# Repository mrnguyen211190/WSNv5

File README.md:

# WSNv5
A small hardware of wireless sensor node

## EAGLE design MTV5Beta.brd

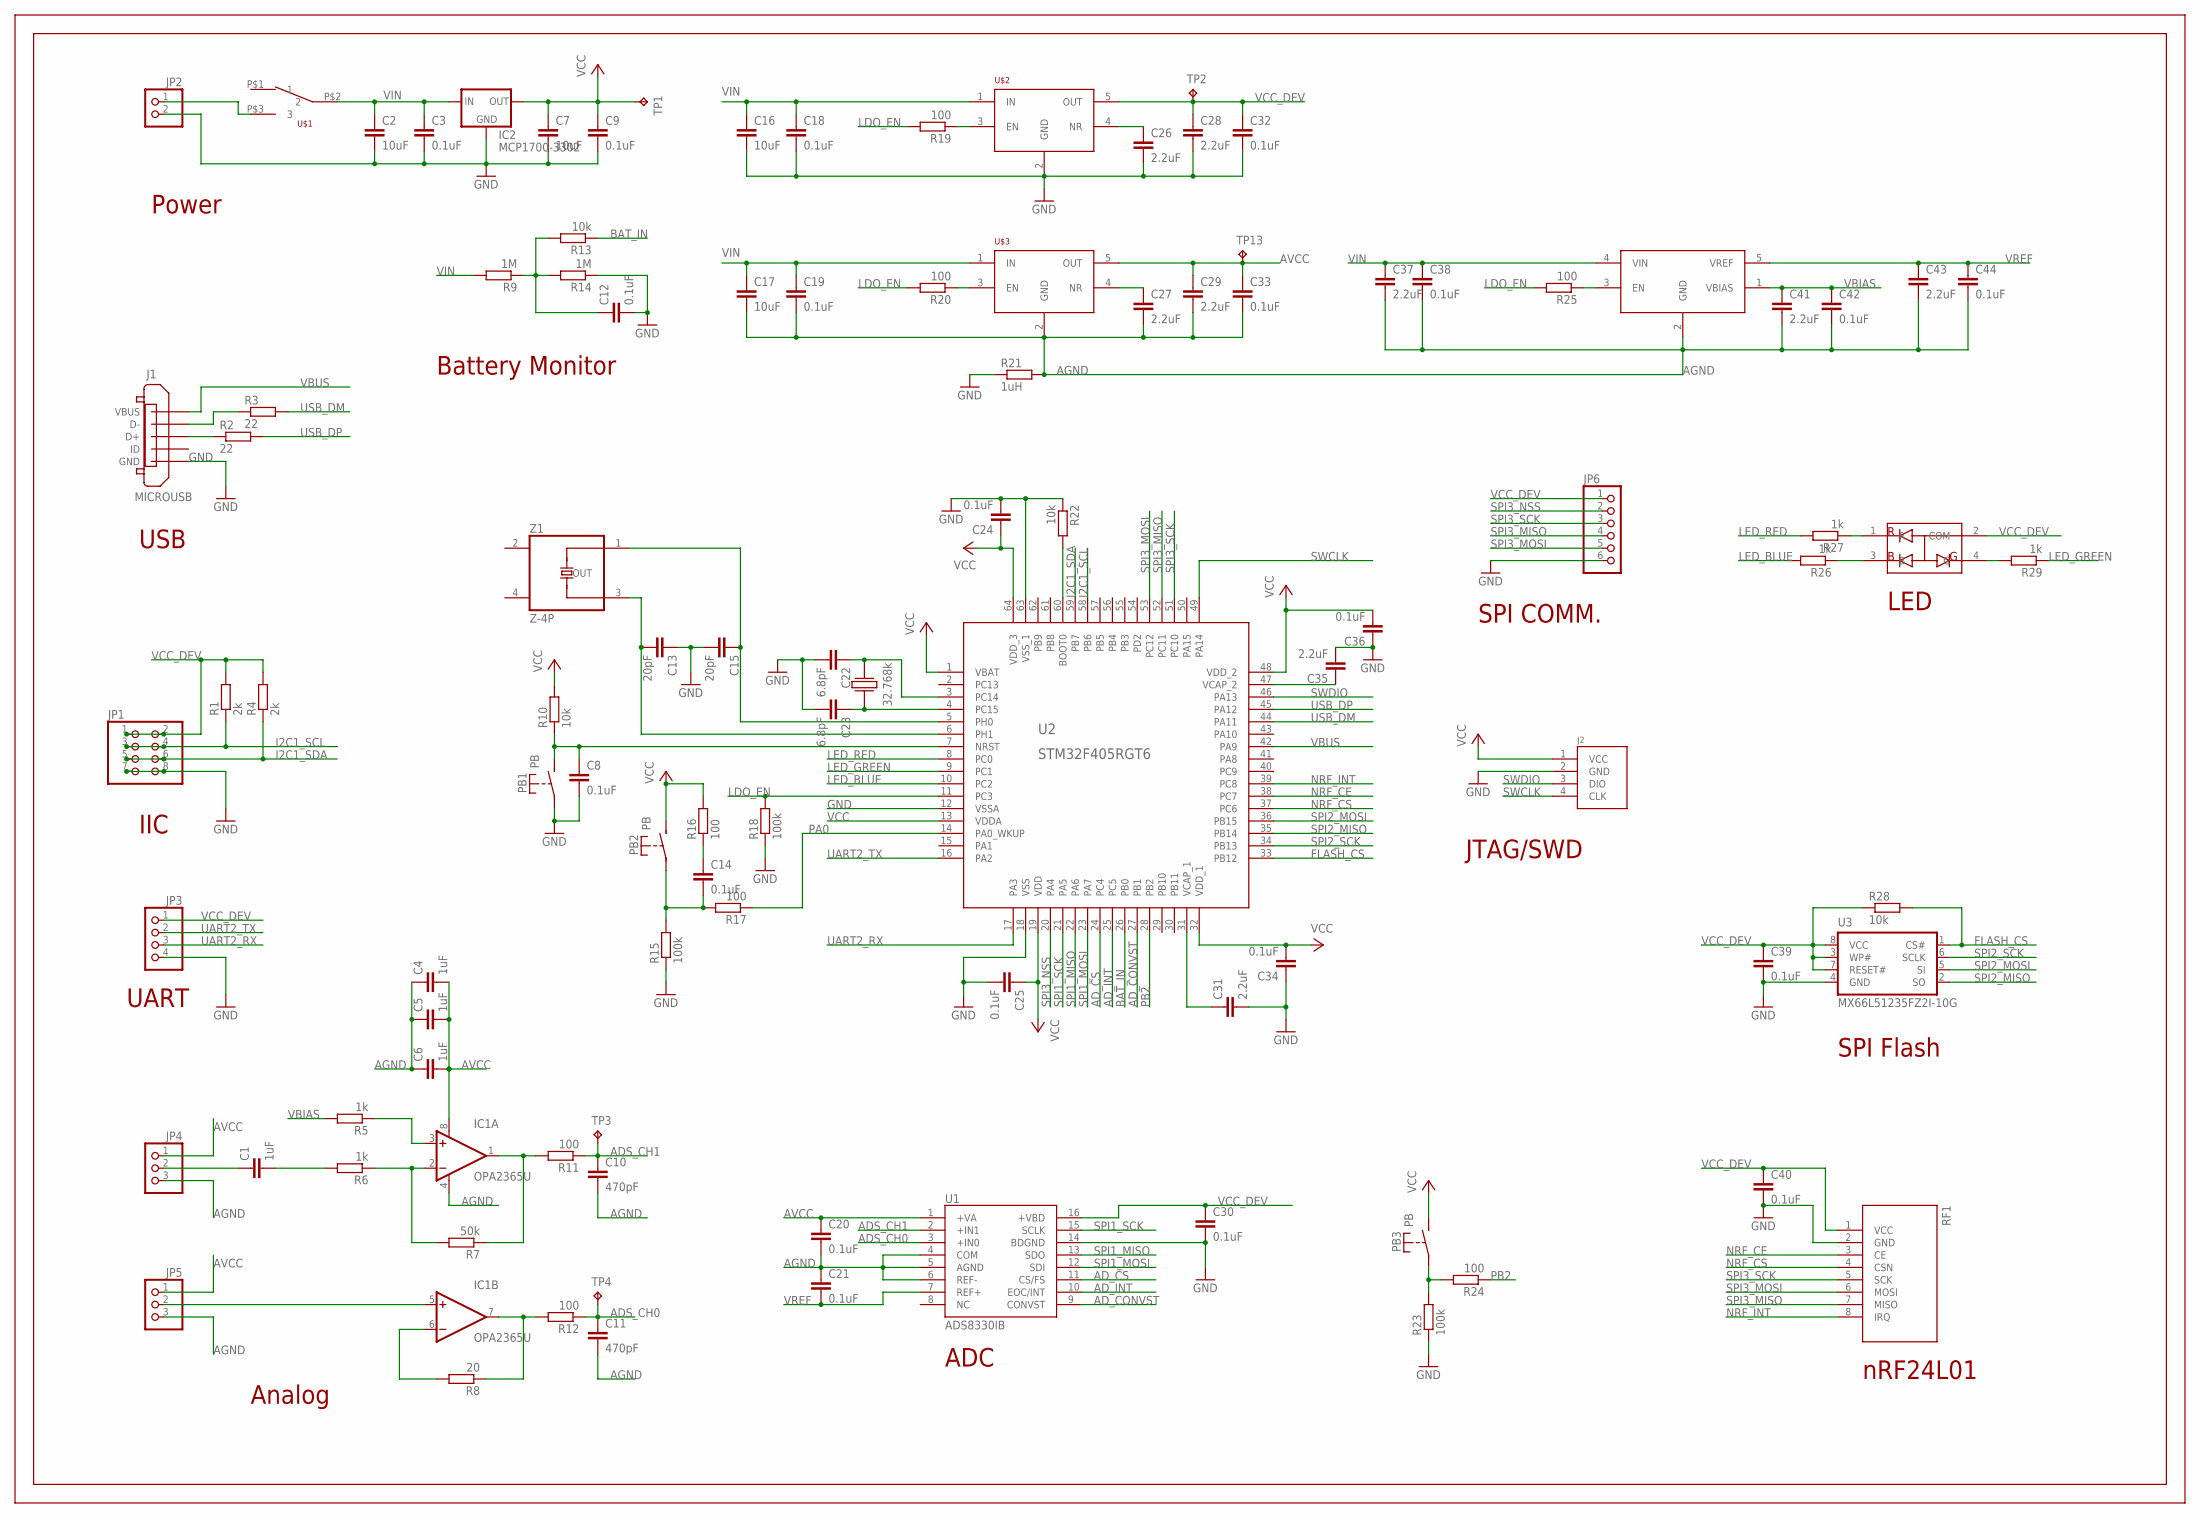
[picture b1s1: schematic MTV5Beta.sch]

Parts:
C1, C4, C5, C6: 1uF; C0603
C2, C7, C16, C17: 10uF; C0603
C3, C8, C9, C12, C14, C18, C19, C20, C21, C24, C25, C30, C32, C33, C34, C36, C38, C39, C40, C42, C44: 0.1uF; C0603
C10, C11: 470pF; C0603
C13, C15: 20pF; C0603
C22, C23: 6.8pF; C0603
C26, C27, C28, C29, C31, C35, C37, C41, C43: 2.2uF; C0603
IC1: OPA2365U; SO08
IC2: MCP1700-3302; SOT23
J1: MICROUSB; MOLEX47346
J2: SWDPORT; 125-4P
JP1: PINHD-2X4; 2X04
JP2: PINHD-1X2; 1X02
JP3: PINHD-1X4; 1X04
JP4, JP5: PINHD-1X3; 1X03
JP6: PINHD-1X6; 1X06
PB1, PB2, PB3: PB; BUTTON
R1, R4: 2k; R0603
R2, R3: 22; R0603
R5, R6, R26, R27, R29: 1k; R0603
R7: 50k; R0603
R8: 20; R0603
R9, R14: 1M; R0603
R10, R13, R22, R28: 10k; R0603
R11, R12, R16, R17, R19, R20, R24, R25: 100; R0603
R15, R18, R23: 100k; R0603
R21: 1uH; R0805
RF1: NRF24L01; NRF24L01-MINI
TP1, TP2, TP3, TP4, TP13: TPB1,27; B1,27
U1: ADS8330IB; TSSOP16
U2: STM32F405RGT6; LQFP64
U3: MX66L51235FZ2I-10G; WSON8L
U$1: 3P-SW; 3P-2-SW
U$2, U$3: TPS73433; SOT-5
U$4: REF2033; SOT-5
U$5: LED-RGB; LED-3228
Z1: Z-4P; ASE
Z2: 32.768k; CM315

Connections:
ADS_CH0: C11.1, R12.1, TP4.TP, U1.3 (+IN0)
ADS_CH1: C10.1, R11.1, TP3.TP, U1.2 (+IN1)
AD_CONVST: U1.9 (CONVST), U2.27 (PB1)
AD_CS: U1.11 (CS/FS), U2.24 (PC4)
AD_INT: U1.10 (EOC/INT), U2.25 (PC5)
AGND: C4.1, C5.1, C6.1, C10.2, C11.2, C17.2, C19.2, C20.2, C21.1, C27.2, C29.2, C33.2, C37.2, C38.2, C41.2, C42.2, C43.2, C44.2, IC1.4 (V-), JP4.3, JP5.3, R21.2, U1.4 (COM), U1.5 (AGND), U1.6 (REF-), U$3.2 (GND), U$4.2 (GND)
AVCC: C4.2, C5.2, C6.2, C20.1, C29.1, C33.1, IC1.8 (V+), JP4.1, JP5.1, TP13.TP, U1.1 (+VA), U$3.5 (OUT)
BAT_IN: R13.1, U2.26 (PB0)
FLASH_CS: R28.2, U2.33 (PB12), U3.1 (CS#)
GND: C2.2, C3.2, C7.2, C8.2, C9.2, C12.2, C13.1, C15.2, C16.2, C18.2, C22.2, C23.2, C24.2, C25.2, C26.2, C28.2, C30.2, C31.2, C32.2, C34.1, C35.2, C36.1, C39.2, C40.2, IC2.1 (GND), J1.5 (GND), J2.2 (GND), JP1.7, JP1.8, JP2.2, JP3.4, JP6.6, PB1.1, R14.1, R15.1, R18.1, R21.1, R22.1, R23.1, RF1.2 (GND), U1.14 (BDGND), U2.12 (VSSA), U2.18 (VSS), U2.63 (VSS_1), U3.4 (GND), U$2.2 (GND)
I2C1_SCL: JP1.3, JP1.4, R1.1, U2.58 (PB6)
I2C1_SDA: JP1.5, JP1.6, R4.1, U2.59 (PB7)
LDO_EN: R18.2, R19.2, R20.2, R25.2, U2.11 (PC3)
LED_BLUE: R26.2, U2.10 (PC2)
LED_GREEN: R29.1, U2.9 (PC1)
LED_RED: R27.2, U2.8 (PC0)
unnamed: R22.2, U2.60 (BOOT0)
unnamed: J1.2 (D-), R3.1
unnamed: J1.3 (D+), R2.1
unnamed: C31.1, U2.31 (VCAP_1)
unnamed: C15.1, U2.5 (PH0), Z1.1 (IO1)
unnamed: C8.1, PB1.2 (S), R10.1, U2.7 (NRST)
unnamed: R19.1, U$2.3 (EN)
unnamed: C13.2, U2.6 (PH1), Z1.3 (IO2)
unnamed: C1.1, JP4.2
unnamed: R25.1, U$4.3 (EN)
unnamed: C35.1, U2.47 (VCAP_2)
unnamed: IC1.5 (+IN), JP5.2
unnamed: IC1.7 (OUT), R8.1, R12.2
unnamed: C12.1, R9.1, R13.2, R14.2
unnamed: IC1.6 (-IN), R8.2
unnamed: C26.1, U$2.4 (NR)
unnamed: JP2.1, U$1.P$3 (3)
unnamed: C14.1, R16.1
unnamed: R27.1, U$5.1 (R)
unnamed: C14.2, PB2.1, R15.2, R17.2
unnamed: R26.1, U$5.3 (B)
unnamed: R29.2, U$5.4 (G)
unnamed: C22.1, U2.3 (PC14), Z2.2 (X2)
unnamed: C23.1, U2.4 (PC15), Z2.1 (X1)
unnamed: PB3.1, R23.2, R24.2
unnamed: R20.1, U$3.3 (EN)
unnamed: C27.1, U$3.4 (NR)
unnamed: IC1.1 (OUT), R7.1, R11.2
unnamed: IC1.3 (+IN), R5.1
unnamed: C1.2, R6.2
unnamed: IC1.2 (-IN), R6.1, R7.2
NRF_CE: RF1.3 (CE), U2.38 (PC7)
NRF_CS: RF1.4 (CSN), U2.37 (PC6)
NRF_INT: RF1.8 (IRQ), U2.39 (PC8)
PA0: R17.1, U2.14 (PA0_WKUP)
PB2: R24.1, U2.28 (PB2)
SPI1_MISO: U1.13 (SDO), U2.22 (PA6)
SPI1_MOSI: U1.12 (SDI), U2.23 (PA7)
SPI1_SCK: U1.15 (SCLK), U2.21 (PA5)
SPI2_MISO: U2.35 (PB14), U3.2 (SO)
SPI2_MOSI: U2.36 (PB15), U3.5 (SI)
SPI2_SCK: U2.34 (PB13), U3.6 (SCLK)
SPI3_MISO: JP6.4, RF1.7 (MISO), U2.52 (PC11)
SPI3_MOSI: JP6.5, RF1.6 (MOSI), U2.53 (PC12)
SPI3_NSS: JP6.2, U2.20 (PA4)
SPI3_SCK: JP6.3, RF1.5 (SCK), U2.51 (PC10)
SWCLK: J2.4 (CLK), U2.49 (PA14)
SWDIO: J2.3 (DIO), U2.46 (PA13)
UART2_RX: JP3.3, U2.17 (PA3)
UART2_TX: JP3.2, U2.16 (PA2)
USB_DM: R3.2, U2.44 (PA11)
USB_DP: R2.2, U2.45 (PA12)
VBIAS: C41.1, C42.1, R5.2, U$4.1 (VBIAS)
VBUS: J1.1 (VBUS), U2.42 (PA9)
VCC: C7.1, C9.1, C24.1, C25.1, C34.2, C36.2, IC2.2 (OUT), J2.1 (VCC), PB2.2 (S), PB3.2 (S), R10.2, R16.2, TP1.TP, U2.1 (VBAT), U2.13 (VDDA), U2.19 (VDD), U2.32 (VDD_1), U2.48 (VDD_2), U2.64 (VDD_3)
VCC_DEV: C28.1, C30.1, C32.1, C39.1, C40.1, JP1.1, JP1.2, JP3.1, JP6.1, R1.2, R4.2, R28.1, RF1.1 (VCC), TP2.TP, U1.16 (+VBD), U3.3 (WP#), U3.7 (RESET#), U3.8 (VCC), U$2.5 (OUT), U$5.2 (COM)
VIN: C2.1, C3.1, C16.1, C17.1, C18.1, C19.1, C37.1, C38.1, IC2.3 (IN), R9.2, U$1.P$2 (2), U$2.1 (IN), U$3.1 (IN), U$4.4 (VIN)
VREF: C21.2, C43.1, C44.1, U1.7 (REF+), U$4.5 (VREF)

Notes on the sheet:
Power
USB
Battery Monitor
IIC
UART
Analog
ADC
nRF24L01
SPI Flash
LED
JTAG/SWD
SPI COMM.

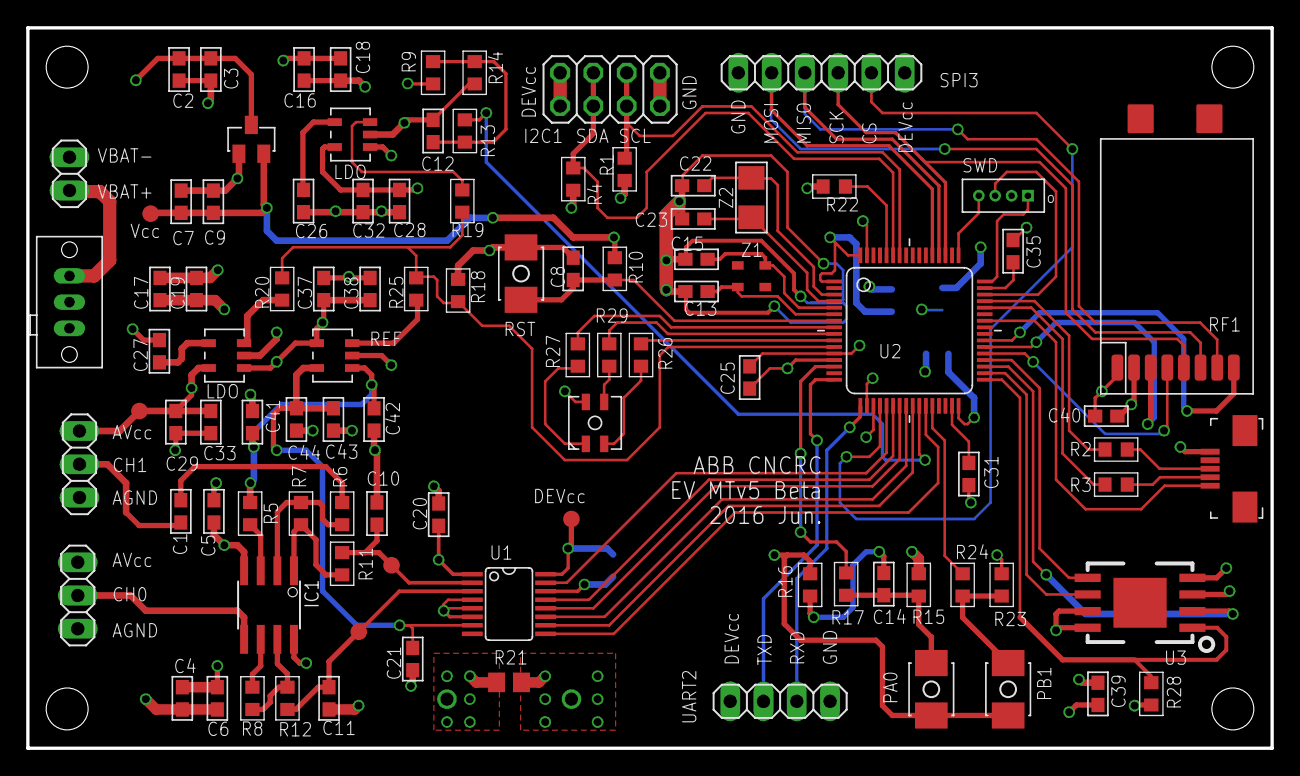
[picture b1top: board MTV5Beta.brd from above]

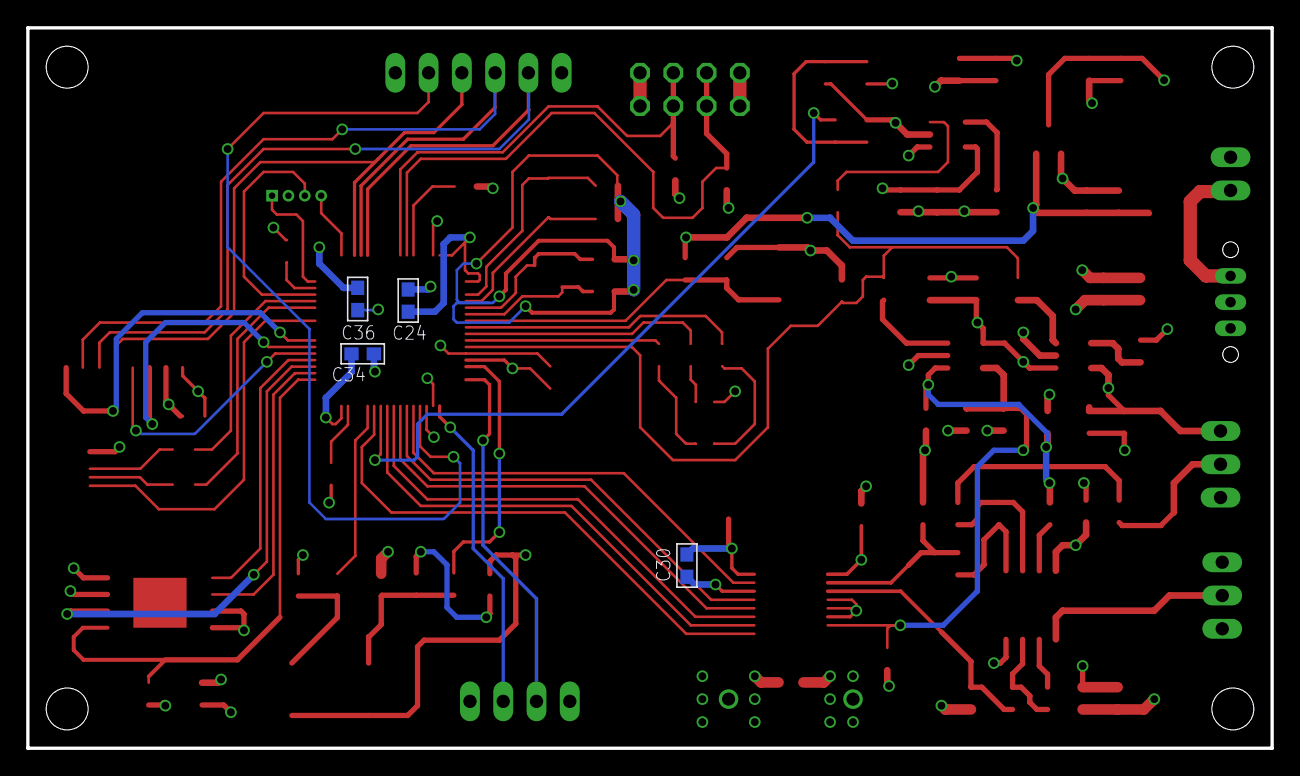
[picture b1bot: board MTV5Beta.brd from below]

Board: 4 copper layers, 95.0 x 55.0 mm, 102 parts (4 on the bottom side), 74 nets.

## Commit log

2016-06-02 Upload initial files
2016-06-03 Upload files
    Upload files
2016-06-04 v1.0 finished
    sch ERC OK!
    pcb DRC OK!
    gerb export OK!
    PDF export OK!
    need adding BOM
